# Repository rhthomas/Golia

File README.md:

# Golia
AVR breakout board for ATxmega64A4U

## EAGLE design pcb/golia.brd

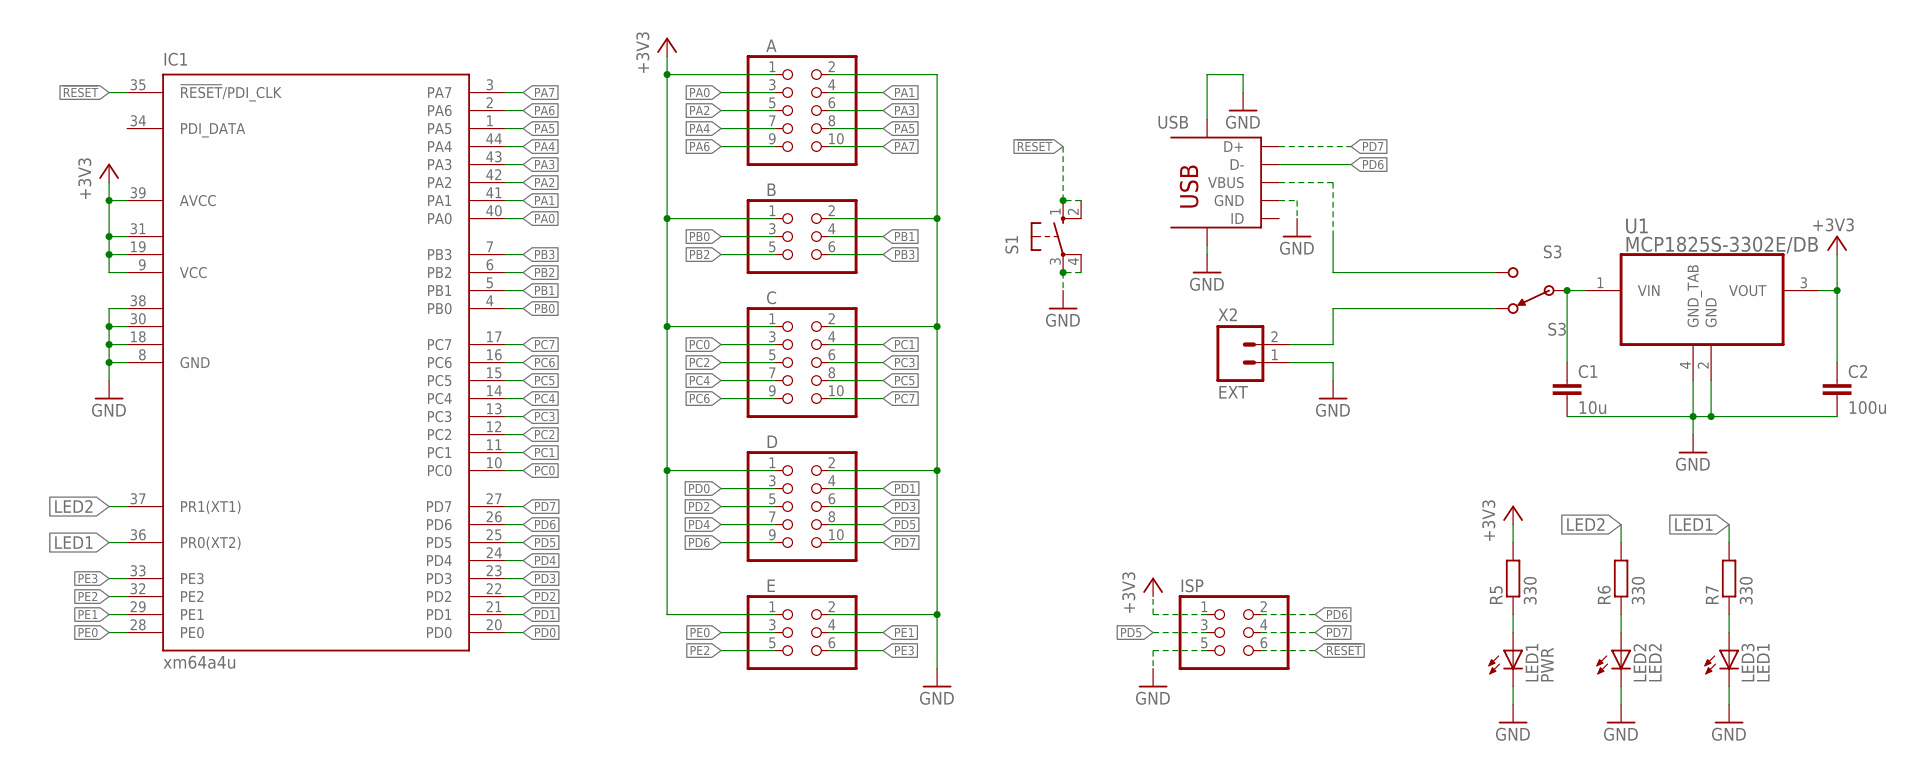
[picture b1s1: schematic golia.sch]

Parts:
A: PINHD-2X5; 2X05
B: PINHD-2X3; 2X03
C: PINHD-2X5; 2X05
C1: 10u; C0603
C2: 100u; C1206
D: PINHD-2X5; 2X05
E: 2X03
IC1: xm64a4u; TQFP44
ISP: PINHD-2X3; 2X03
LED1: PWR; CHIP-LED0805
LED2: LED2; CHIP-LED0805
LED3: LED1; CHIP-LED0805
R5, R6, R7: 330; R0603
S1: 10-XX; B3F-10XX
S3: S3; EG-1218
U1: MCP1825S-3302E/DB; SOT230P700X180-4N
USB: USB-MINIB-PTH
X2: EXT; JST-2-2MM-PTH-VERT-LOCK

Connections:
!RESET: IC1.35 (!RESET!/PDI_CLK), ISP.6, S1.1 (S), S1.2 (S1)
+3V3: A.1, B.1, C.1, C2.1, D.1, E.1, IC1.9 (VCC), IC1.19 (VCC1), IC1.31 (VCC2), IC1.39 (AVCC), ISP.1, R5.2, U1.3 (VOUT)
GND: A.2, B.2, C.2, C1.2, C2.2, D.2, E.2, IC1.8 (GND), IC1.18 (GND1), IC1.30 (GND2), IC1.38 (GND3), ISP.5, LED1.C, LED2.C, LED3.C, S1.3, S1.4 (P1), U1.2 (GND), U1.4 (GND_TAB), USB.GND, USB.P$6 (SHD1), USB.P$7 (SHD2), X2.1
LED1: IC1.36 (PR0(XT2)), R7.2
LED2: IC1.37 (PR1(XT1)), R6.2
unnamed: S3.1, X2.2
unnamed: S3.3 (2), USB.VBUS
unnamed: C1.1, S3.2 (C), U1.1 (VIN)
unnamed: LED1.A, R5.1
unnamed: LED2.A, R6.1
unnamed: LED3.A, R7.1
PA0: A.3, IC1.40 (PA0)
PA1: A.4, IC1.41 (PA1)
PA2: A.5, IC1.42 (PA2)
PA3: A.6, IC1.43 (PA3)
PA4: A.7, IC1.44 (PA4)
PA5: A.8, IC1.1 (PA5)
PA6: A.9, IC1.2 (PA6)
PA7: A.10, IC1.3 (PA7)
PB0: B.3, IC1.4 (PB0)
PB1: B.4, IC1.5 (PB1)
PB2: B.5, IC1.6 (PB2)
PB3: B.6, IC1.7 (PB3)
PC0: C.3, IC1.10 (PC0)
PC1: C.4, IC1.11 (PC1)
PC2: C.5, IC1.12 (PC2)
PC3: C.6, IC1.13 (PC3)
PC4: C.7, IC1.14 (PC4)
PC5: C.8, IC1.15 (PC5)
PC6: C.9, IC1.16 (PC6)
PC7: C.10, IC1.17 (PC7)
PD0: D.3, IC1.20 (PD0)
PD1: D.4, IC1.21 (PD1)
PD2: D.5, IC1.22 (PD2)
PD3: D.6, IC1.23 (PD3)
PD4: D.7, IC1.24 (PD4)
PD5: D.8, IC1.25 (PD5), ISP.3
PD6: D.9, IC1.26 (PD6), ISP.2, USB.D-
PD7: D.10, IC1.27 (PD7), ISP.4, USB.D+
PE0: E.3, IC1.28 (PE0)
PE1: E.4, IC1.29 (PE1)
PE2: E.5, IC1.32 (PE2)
PE3: E.6, IC1.33 (PE3)

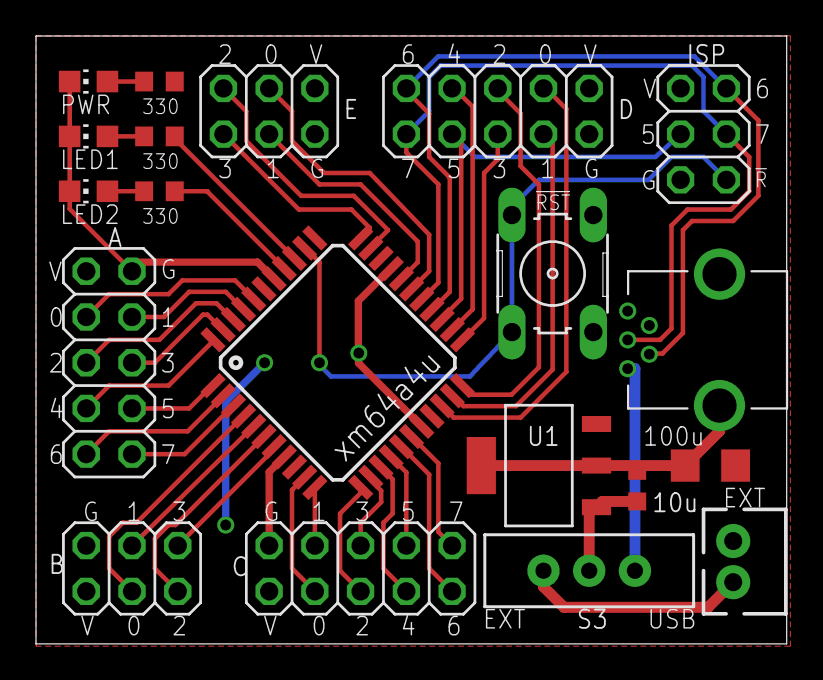
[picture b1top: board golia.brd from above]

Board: 2 copper layers, 41.7 x 33.8 mm, 20 parts (0 on the bottom side), 43 nets.

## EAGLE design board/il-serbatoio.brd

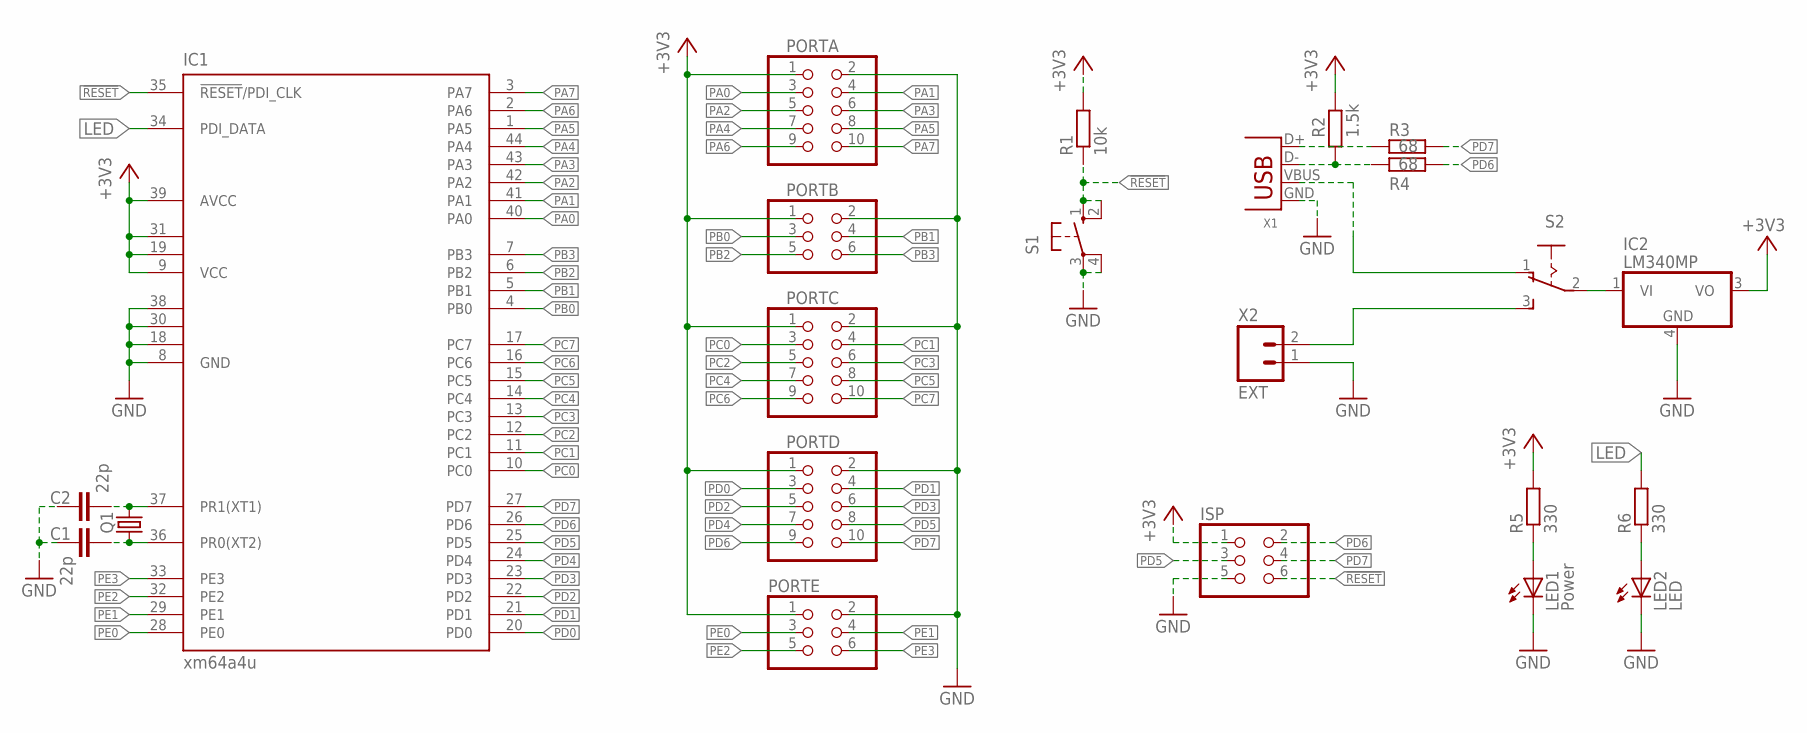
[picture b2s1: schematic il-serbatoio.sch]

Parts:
C1, C2: 22p; C025-024X044
IC1: xm64a4u; TQFP44
IC2: LM340MP; SOT223
ISP: PINHD-2X3; 2X03
LED1: Power; CHIP-LED0805
LED2: LED; CHIP-LED0805
PORTA: PINHD-2X5; 2X05
PORTB: PINHD-2X3; 2X03
PORTC: PINHD-2X5; 2X05
PORTD: PINHD-2X5; 2X05
PORTE: PINHD-2X3; 2X03
Q1: CRYSTALCTS406; CTS406
R1: 10k; M0805
R2: 1.5k; M0805
R3, R4: 68; M0805
R5, R6: 330; M0805
S1: 10-XX; B3F-10XX
S2: 255SB
X1: USB-MB-S
X2: EXT; JST-2-2MM-PTH-VERT-LOCK

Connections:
!RESET: IC1.35 (!RESET!/PDI_CLK), ISP.6, R1.1, S1.1 (S), S1.2 (S1)
+3V3: IC1.9 (VCC), IC1.19 (VCC1), IC1.31 (VCC2), IC1.39 (AVCC), IC2.3 (VO), ISP.1, PORTA.1, PORTB.1, PORTC.1, PORTD.1, PORTE.1, R1.2, R2.2, R5.2
GND: C1.1, C2.1, IC1.8 (GND), IC1.18 (GND1), IC1.30 (GND2), IC1.38 (GND3), IC2.4 (GND), ISP.5, LED1.C, LED2.C, PORTA.2, PORTB.2, PORTC.2, PORTD.2, PORTE.2, S1.3, S1.4 (P1), X1.GND, X2.1
LED: IC1.34 (PDI_DATA), R6.2
unnamed: S2.3 (S), X2.2
unnamed: S2.1 (O), X1.VBUS
unnamed: R2.1, R4.1, X1.D-
unnamed: R3.1, X1.D+
unnamed: IC2.1 (VI), S2.2
unnamed: LED1.A, R5.1
unnamed: LED2.A, R6.1
unnamed: C1.2, IC1.36 (PR0(XT2)), Q1.1
unnamed: C2.2, IC1.37 (PR1(XT1)), Q1.3 (2)
PA0: IC1.40 (PA0), PORTA.3
PA1: IC1.41 (PA1), PORTA.4
PA2: IC1.42 (PA2), PORTA.5
PA3: IC1.43 (PA3), PORTA.6
PA4: IC1.44 (PA4), PORTA.7
PA5: IC1.1 (PA5), PORTA.8
PA6: IC1.2 (PA6), PORTA.9
PA7: IC1.3 (PA7), PORTA.10
PB0: IC1.4 (PB0), PORTB.3
PB1: IC1.5 (PB1), PORTB.4
PB2: IC1.6 (PB2), PORTB.5
PB3: IC1.7 (PB3), PORTB.6
PC0: IC1.10 (PC0), PORTC.3
PC1: IC1.11 (PC1), PORTC.4
PC2: IC1.12 (PC2), PORTC.5
PC3: IC1.13 (PC3), PORTC.6
PC4: IC1.14 (PC4), PORTC.7
PC5: IC1.15 (PC5), PORTC.8
PC6: IC1.16 (PC6), PORTC.9
PC7: IC1.17 (PC7), PORTC.10
PD0: IC1.20 (PD0), PORTD.3
PD1: IC1.21 (PD1), PORTD.4
PD2: IC1.22 (PD2), PORTD.5
PD3: IC1.23 (PD3), PORTD.6
PD4: IC1.24 (PD4), PORTD.7
PD5: IC1.25 (PD5), ISP.3, PORTD.8
PD6: IC1.26 (PD6), ISP.2, PORTD.9, R4.2
PD7: IC1.27 (PD7), ISP.4, PORTD.10, R3.2
PE0: IC1.28 (PE0), PORTE.3
PE1: IC1.29 (PE1), PORTE.4
PE2: IC1.32 (PE2), PORTE.5
PE3: IC1.33 (PE3), PORTE.6

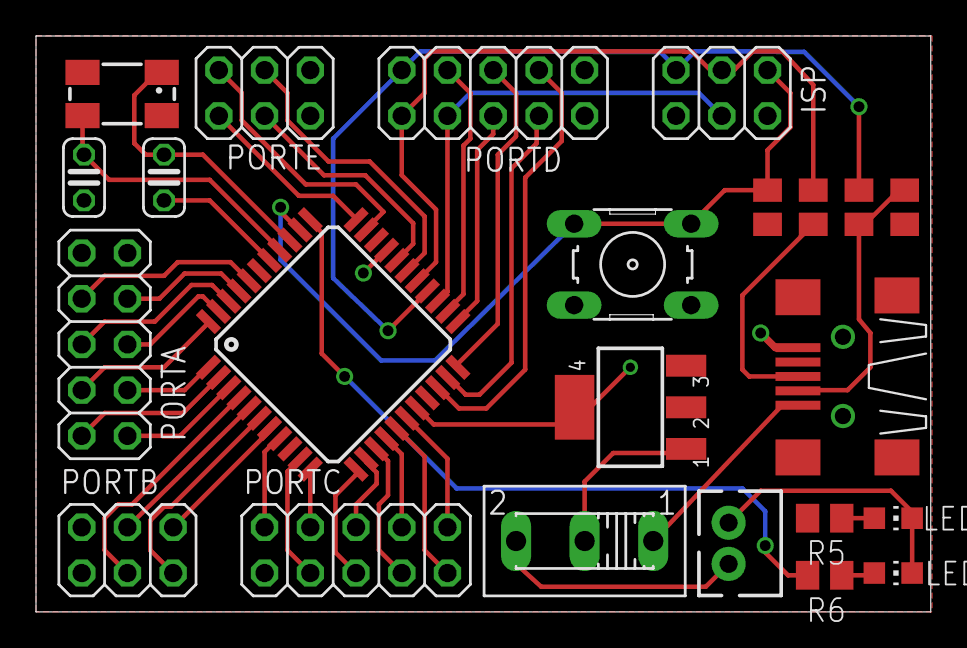
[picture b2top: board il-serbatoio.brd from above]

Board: 2 copper layers, 49.7 x 32.0 mm, 23 parts (0 on the bottom side), 45 nets.

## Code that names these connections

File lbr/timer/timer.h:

/***************************************************************************//**
 * @file   timer.h
 * @author Tom Darlison
 * @date   2017-06-09
 * @brief  Custom library for the AVR xmega series for timer0/1/2.
 ******************************************************************************/

#ifndef TIMER_H
#define TIMER_H

// includes
#include <avr/io.h>
#include <stdint.h>
#include <avr/interrupt.h>

#define MAX_TOP  65535	// = 1<<16 - 1
#define MAX_TOP2 255	// = 1<<8  - 1

typedef enum {TC0 = 0, TC1, TC2} timerType;

// todo
// 
// add in all timer 2 functionailty 
// 		- make sure timer 0 runs in normal mode
// 		- timer 2 runs in split mode
// add in timer 2 set compare and port output
// ISR for timer 2 in normal mode
// set compare/duty -> optimise for 2 chanel on timer 1
// 

class Timer
{
public: // members
public: // methods
	// c/d-tor
	Timer(TC0_struct TC);
	Timer(TC1_struct TC);
	Timer(TC2_struct TC);
	~Timer();

	// set freqency of timer
	void setFreq(const float & freq);
	void setPeriod_s (const float & period);
	void setPeriod_ms(const float & period);
	void setPeriod_us(const float & period);
	float getFreq() const;
	uint16_t getTop() const;

	// set mode and output of waves
	void setTick(const float & freq); // OVF_vect
	void setMode(const unsigned char mode);
	void portOverride(const bool A, const bool B, const bool C, const bool D);

	// set Comparitor values
	void setCompare (const unsigned int A, const unsigned int B, 
					 const unsigned int C, const unsigned int D);
	void setCompareA(const unsigned int A);
	void setCompareB(const unsigned int B);
	void setCompareC(const unsigned int C);
	void setCompareD(const unsigned int D);

	// PWM mode
	void initPWM (const float & freq, 
				  const float & A, const float & B, 
				  const float & C, const float & D);
	void setDuty (const float & A, const float & B, 
				  const float & C, const float & D);
	void setDutyA(const float & A);
	void setDutyB(const float & B);
	void setDutyC(const float & C);
	void setDutyD(const float & D);
private: // members
	const timerType _type;
	union {
		TC0_struct* p_TC0;
		TC1_struct* p_TC1;
		TC2_struct* p_TC2;
	}; // only need 1 of these pointers in the class once made
	float _frequency; 
	uint16_t _TOP;
private: // methods
	void clockSetUp(const unsigned char & clkDivider, const int & TOP);
};

#endif // TIMER_H

/*

// NOTE: TC0 and TC2 use same hardware 
// therefore cannot coexist on same port

PIN		TCn0	TCn1	TCn2

PC0	 	OC0A			LCMPA
PC1	 	OC0B			LCMPB
PC2	 	OC0C			LCMPC
PC3	 	OC0D			LCMPD
PC4				OC1A	HCMPA
PC5				OC1B	HCMPB
PC6	 					HCMPC
PC7	 					HCMPD

PD0		OC0A			LCMPA
PD1		OC0B			LCMPB
PD2		OC0C			LCMPC
PD3		OC0D			LCMPD
PD4				OC1A	HCMPA
PD5				OC1B	HCMPB
PD6	 					HCMPC
PD7	 					HCMPD

PE0		OC0A			
PE1		OC0B			
PE2		OC0C			
PE3		OC0D			
	
*/

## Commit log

2017-03-20 First commit of libraries folder.
2017-03-20 Added current files to repo
2017-03-20 Added board files to repo
2017-03-20 First commit of eagle files.
2017-03-20 Renamed board files and folder.
2017-03-20 Removed old description.
2017-03-20 Removed RFM library. Will build from ground up.
2017-03-20 Made the constructor and destrictor private since the user will not need them; Serial, Serial1, Serial2 etc have already been instanciated. Need to complete the #defines for all 4 UARTs then change t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
2017-03-20 Removed #defines. Using register offset method instead.
2017-03-20 Implimented address offset for SerialClass constructor.
2017-03-20 Finished function content.
    Compiled first test with examples/printing.cpp however they failed. The method
    of using uint8_t* might not be working, USART** defines are not uint8_t* type
    but rather UART_t types?
2017-03-20 New method of handling different UART registers. Compiled successfully.
2017-03-23 Changed component packages
2017-03-23 Changed layout of board, USB now central
2017-03-23 created gitignore
2017-03-23 added ignores for board and schematic backups
2017-03-31 Styling Change
    No functional change.
2017-04-09 Added Silkscreen for ports
2017-04-09 Modified doxygen styling.
2017-04-09 Updated other files to new doxy-style.
2017-04-09 * Swapped out the power switch, regulator, and USB connector with those available free from the uni * Fattened up some of the power supply traces.
2017-04-09 Added names to silk screen increased board size to fit port silks
2017-04-16 Changes to LEDs
2017-04-17 Changed to ingnore Eagle locks
2017-04-17 Reduced width and removed !RST pullup
2017-04-17 Reduced width of board
2017-04-20 Reduced width to 42mm, removed USB series resistors
2017-04-27 Added example code makefile.
    * Classes now use `this->` notation for setting member values.
2017-04-27 Initial library standards.
2017-04-27 Objects now in `Makefile.in`
2017-04-30 Discovered PORT register are different on xmega.
    * PORTB_DIR defines whether pins are input or output (DDRB)
    * PORTB_OUT sets the value of the pins (PORTB)
    * Todo: inside functions make the PORTB_OUT not be fixed to that port.
2017-05-02 Removed build/ directory.
2017-05-02 Added missing bit masks.
2017-05-02 Initial commit of onboard LED controller
2017-05-02 Removed unneeded library
2017-05-02 Changed wrong operation for off function
2017-05-03 Added bill of materials for labs
2017-05-03 Corrected silk screen and measurement layering
2017-05-03 Changed structure from class to functions
2017-05-04 Constructor now takes port as an argument.
2017-05-04 Changed a few comments.
2017-05-31 Inital commit for virtual ports code
2017-06-01 No cpp functionality.
2017-06-10 Added size of binary output option
2017-06-11 corrected init function
2017-06-15 Initial commit of Timer Library
2017-06-15 Deleted object files
2017-06-16 added more functionality
